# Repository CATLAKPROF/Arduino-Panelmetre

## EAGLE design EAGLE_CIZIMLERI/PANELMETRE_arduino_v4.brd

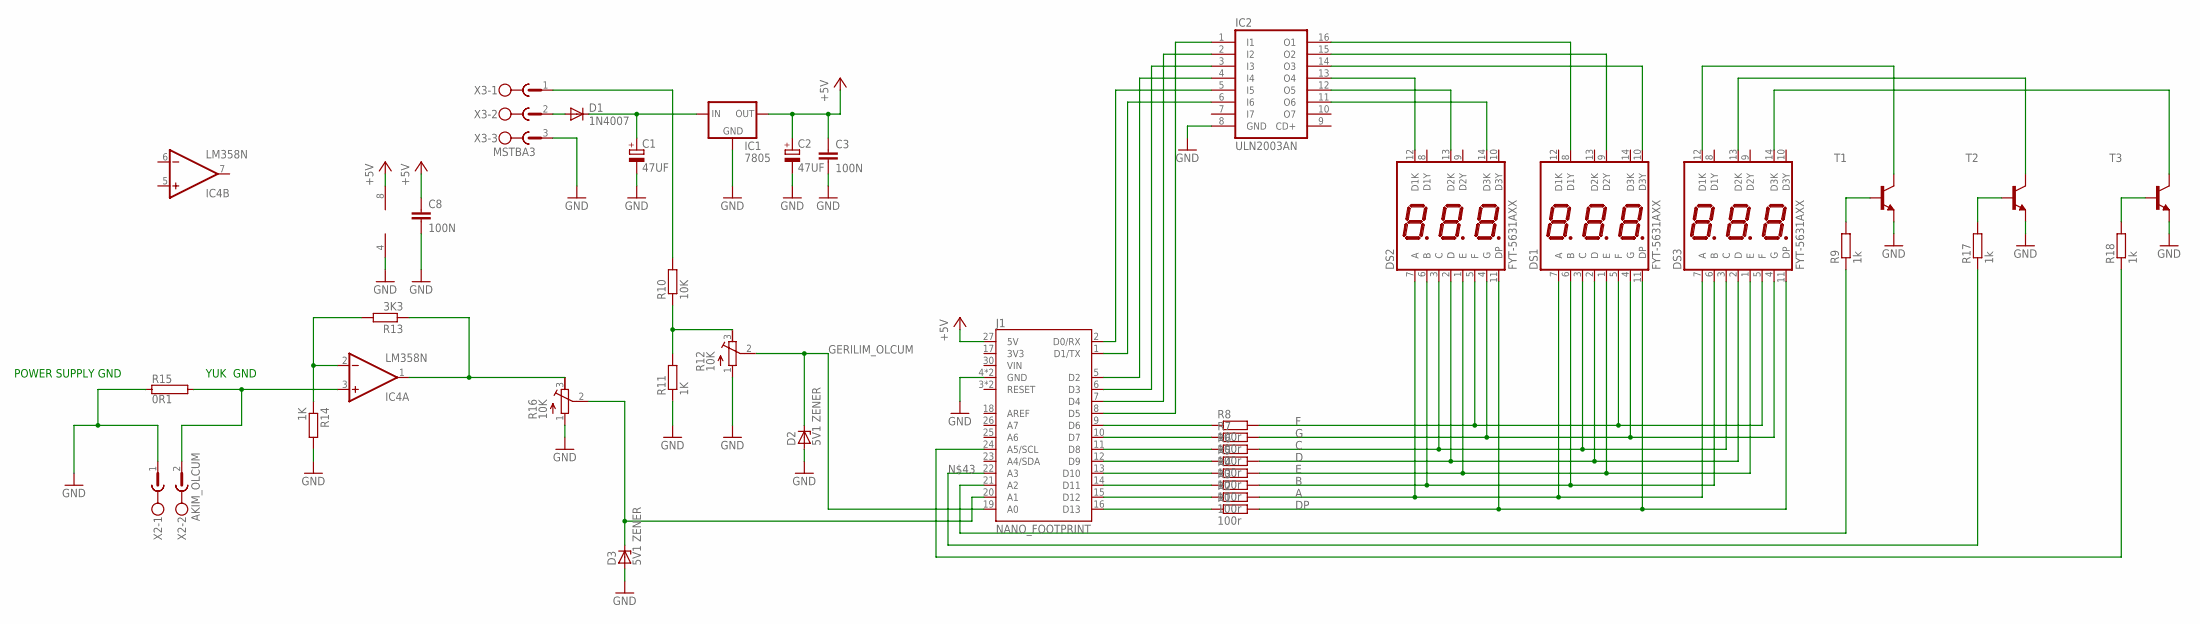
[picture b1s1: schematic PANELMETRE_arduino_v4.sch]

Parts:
C1, C2: 47UF; E2-4
C3, C8: 100N; C050-024X044
D1: 1N4007; DO35-10
D2, D3: 5V1 ZENER; DO35Z10
DS1, DS2, DS3: FYT-5631AXX; DISPLAY
IC1: 7805; 78MXXL
IC2: ULN2003AN; DIL16
IC4: LM358N; DIL08
J1: NANO_FOOTPRINT; NANO
R1, R2, R3, R4, R5, R6, R7, R8: 100r; 0207/10
R9, R17, R18: 1k; 0207/10
R10: 10K; 0207/10
R11, R14: 1K; 0207/10
R12, R16: 10K; RTRIM64W
R13: 3K3; 0207/10
R15: 0R1; RS10_38-39
T1, T2, T3: BC237-NPN-TO92-CBE; TO92-CBE
X2: AKIM_OLCUM; MSTBA2
X3: MSTBA3

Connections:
+5V: C2.+, C3.1, C8.1, IC1.OUT, IC4.8 (V+), J1.27 (5V)
A: DS1.7 (A), DS2.7 (A), DS3.7 (A), R2.2
AKIM_OLCUM: D3.C, J1.20 (A1), R16.2 (S)
B: DS1.6 (B), DS2.6 (B), DS3.6 (B), R3.2
C: DS1.3 (C), DS2.3 (C), DS3.3 (C), R6.2
D: DS1.2 (D), DS2.2 (D), DS3.2 (D), R5.2
DP: DS1.11 (DP), DS2.11 (DP), DS3.11 (DP), R1.2
E: DS1.1 (E), DS2.1 (E), DS3.1 (E), R4.2
F: DS1.5 (F), DS2.5 (F), DS3.5 (F), R8.2
G: DS1.4 (G), DS2.4 (G), DS3.4 (G), R7.2
GERILIM_OLCUM: D2.C, J1.19 (A0), R12.2 (S)
GND: C1.-, C2.-, C3.2, C8.2, D2.A, D3.A, IC1.GND, IC2.8 (GND), IC4.4 (V-), J1.4 (GND), J1.29 (GND), R11.1, R12.1 (A), R14.2, R15.1, R16.1 (A), T1.E, T2.E, T3.E, X2.1, X3.3
unnamed: J1.16 (D13), R1.1
unnamed: J1.15 (D12), R2.1
unnamed: J1.14 (D11), R3.1
unnamed: J1.13 (D10), R4.1
unnamed: J1.12 (D9), R5.1
unnamed: J1.11 (D8), R6.1
unnamed: J1.10 (D7), R7.1
unnamed: J1.9 (D6), R8.1
unnamed: DS1.8 (D1Y), IC2.16 (O1)
unnamed: DS1.9 (D2Y), IC2.15 (O2)
unnamed: DS1.10 (D3Y), IC2.14 (O3)
unnamed: DS2.12 (D1K), IC2.13 (O4)
unnamed: DS2.13 (D2K), IC2.12 (O5)
unnamed: DS2.14 (D3K), IC2.11 (O6)
unnamed: IC2.1 (I1), J1.8 (D5)
unnamed: IC2.2 (I2), J1.7 (D4)
unnamed: IC2.3 (I3), J1.6 (D3)
unnamed: IC2.4 (I4), J1.5 (D2)
unnamed: IC2.6 (I6), J1.1 (D1/TX)
unnamed: IC2.5 (I5), J1.2 (D0/RX)
unnamed: D1.A, X3.2
unnamed: C1.+, D1.C, IC1.IN
unnamed: R10.2, X3.1
unnamed: IC4.2 (-IN), R13.2, R14.1
unnamed: R10.1, R11.2, R12.3 (E)
unnamed: DS3.12 (D1K), T1.C
unnamed: DS3.13 (D2K), T2.C
unnamed: IC4.3 (+IN), R15.2, X2.2
unnamed: IC4.1 (OUT), R13.1, R16.3 (E)
unnamed: DS3.14 (D3K), T3.C
unnamed: R9.2, T1.B
unnamed: R17.2, T2.B
unnamed: R18.2, T3.B
unnamed: J1.21 (A2), R9.1
unnamed: J1.22 (A3), R17.1
unnamed: J1.24 (A5/SCL), R18.1

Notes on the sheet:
POWER SUPPLY GND
YUK GND

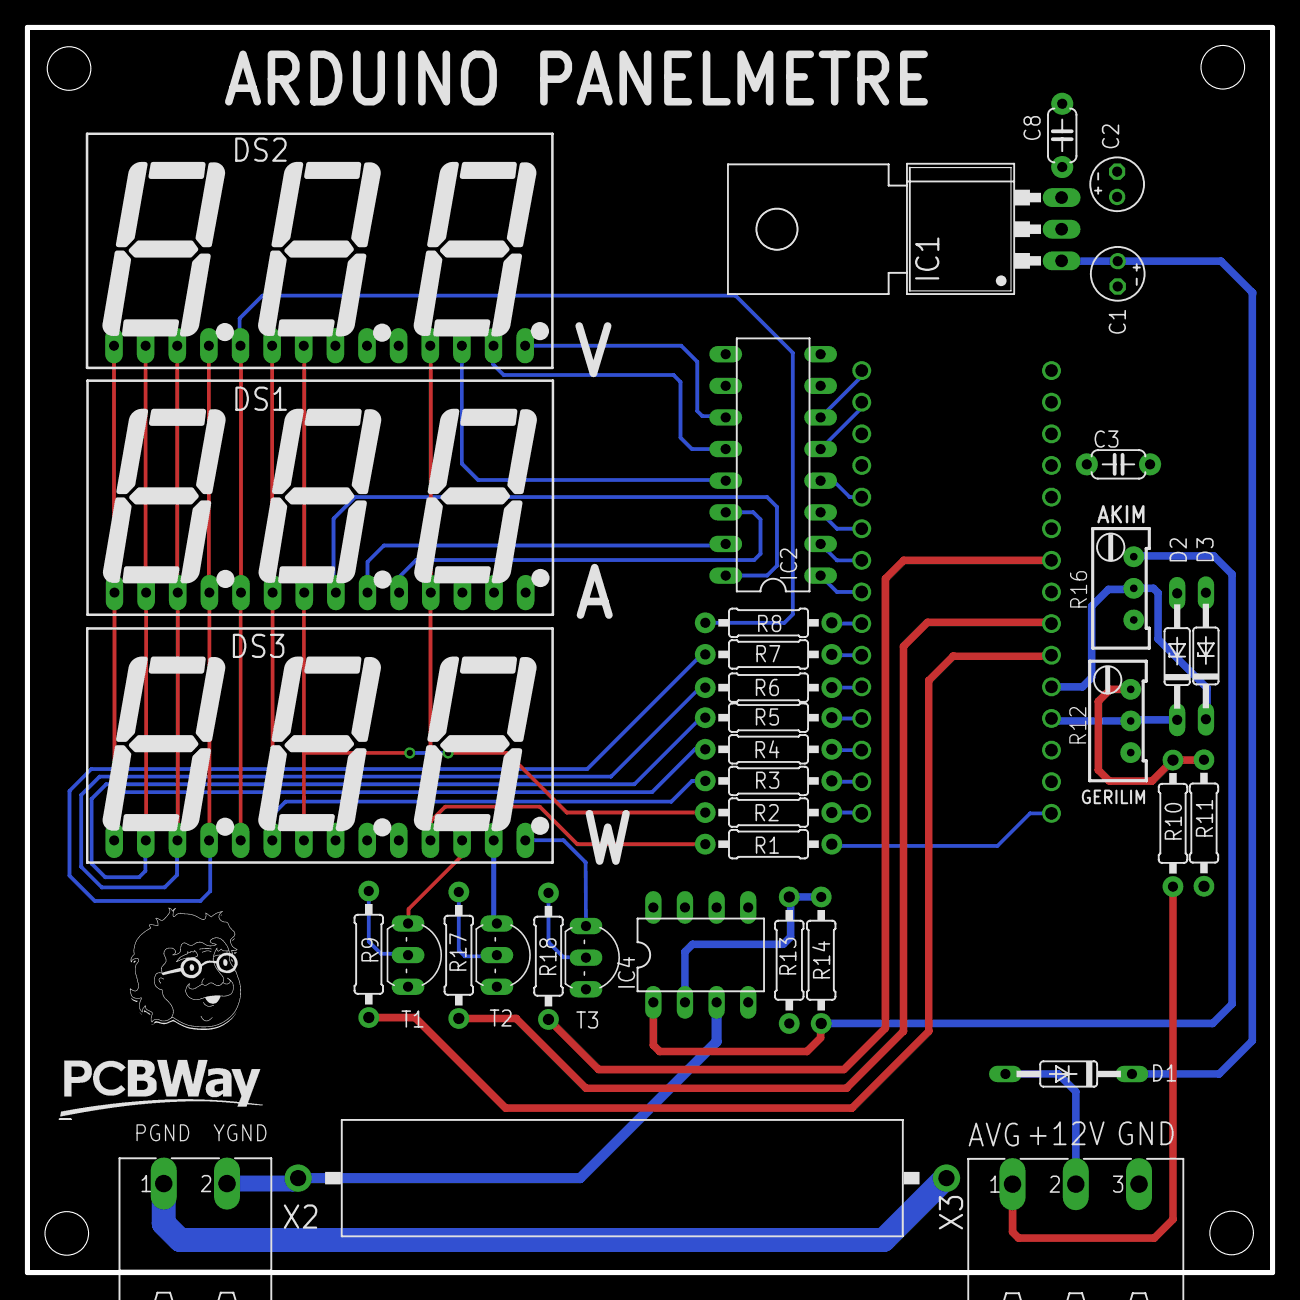
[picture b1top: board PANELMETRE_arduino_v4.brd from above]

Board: 2 copper layers, 100.0 x 100.0 mm, 37 parts (0 on the bottom side), 48 nets.

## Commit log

2021-03-17 Arduino ile Panelmetre
    Atölyelerin vazgeçilmezi voltmete,ampermetre ve wattmetre yi tek bir pcb de toplayıp PANELMETRE ürettik. Detaylar youtube kanalımda....

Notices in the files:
parts and their libraries:
SparkFun-Boards: Licensing: Creative Commons ShareAlike 4.0 International - https://creativecommons.org/licenses/by-sa/4.0
